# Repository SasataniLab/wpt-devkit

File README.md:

# wpt-devkit-v0.1 SCPI Command Set
Hardware tool and Arduino library for developing wireless power applications.

## Command reference
[SCPI command reference](./docs/SCPI.md)

## Arduino IDE
### Installation
Add `wpt-io-arduino.zip` in release.
- Sketch -> Include Library -> Add .ZIP Library

### Dependencies
**Manual ZIP install**
- [bschulz1701/PAC1720_Library](https://github.com/bschulz1701/PAC1720_Library)

**Arduino Library Manager**
- [WifWaf/MCP45HVX1](https://github.com/WifWaf/MCP45HVX1)

### Update
You need to manually uninstall to update. We plan to add this to Arduino Library Manager to automate this in the future.

## Examples
See [Examples](./firmware/wpt-io-arduino/examples) for example Arduino sketches

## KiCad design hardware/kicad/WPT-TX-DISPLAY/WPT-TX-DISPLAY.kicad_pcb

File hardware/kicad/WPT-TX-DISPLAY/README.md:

# WPT-TX-DISPLAY: 表示基板（仮設計）

送電基板 `WPT-01-TRANSMITTER`（`../WPT-TX`、改訂 7）の J2（2 × 6）に挿す表示用の子基板（v0.2）。0.96 型の IPS TFT（80 × 160 画素、ST7735S）を 1 個載せる。3.3 V だけで動く。設計の考え方、重なり方の図、表示器の入手先、確かめていないことは [`docs/stm32-tx/display_shield_study.md`](../../../docs/stm32-tx/display_shield_study.md) にまとめた。

状態（2026-11-17）: 回路図の ERC 0 件、基板の DRC（回路図との照合つき）0 件。実物では組んでいない。

## ファイル

| ファイル | 内容 |
|---|---|
| `WPT-TX-DISPLAY.kicad_sch` / `.kicad_pcb` / `.kicad_pro` | 回路図（1 枚）、基板（2 層、30.4 × 14.8 mm）、プロジェクト（設計ルールは送電基板と同じ） |
| `lib/` | 表示器のシンボルとフットプリント（`WPT_Display`） |
| `tools/build.sh` | 回路図 → ERC → ネットリスト → 基板 → DRC を通して実行する |
| `tools/gen_sch.py`、`tools/schgen.py` | 回路図を書くスクリプトと、その下請け |
| `tools/make_board.py` | ネットリストから基板を作る（外形、配置、配線、ベタ、シルク） |
| `tools/make_footprint.py` | 表示器のフットプリントを作る。フレキの寸法の出どころもここに書いてある |
| `tools/drawings.py` | 文書の図 3 枚を、送電基板とこの基板のファイルから作る |
| `tools/drc_summary.py` | DRC の結果（JSON）の件数を表示する |
| `fab/export.sh`、`fab/bom_extra.csv` | 製造データの出力と、基板データに無い部品の表（今は空） |

## 作り直す

KiCad 10（`kicad-cli` と `pcbnew` の Python モジュール）が要る。

```sh
cd hardware/kicad/WPT-TX-DISPLAY
sh tools/build.sh        # 終了コード 0 なら ERC・DRC とも 0 件
sh fab/export.sh         # fab/out/ にガーバー、ドリル、BOM、部品座標、図面
python3 tools/drawings.py ../WPT-TX/WPT-01-TRANSMITTER.kicad_pcb WPT-TX-DISPLAY.kicad_pcb \
    ../../../docs/stm32-tx/img/display_plan.png ../../../docs/stm32-tx/img/display_side.png ../../../docs/stm32-tx/img/display_board.png
```

- 回路図と基板はスクリプトが書く。定数や寸法を変えるときはスクリプトを直して `tools/build.sh` を実行する。KiCad で開いて手で直すこともできるが、スクリプトを再実行すると上書きされる。
- 基板の座標は送電基板と同じにしてある。この基板の点 (x, y) は、送電基板の同じ座標の点の 9.9 mm 上にある。
- `fab/out/` は git 管理外。発注用の一式は `../release/WPT-TX-DISPLAY_v0.2/` に置いてある。

## 発注するとき

- 基板: 2 層、1.6 mm、30.4 × 14.8 mm の長方形（角は R1.0）。最小線幅 / 間隔 0.2 / 0.2 mm、ビア 0.6 / 0.3 mm（Tenting vias = レジストで覆う）。
- 実装: 裏面だけ、すべて表面実装（C1、C2、R1、R2、Q1 と、ソケット J1 = Samtec SSM-106-L-DV）。
- **表示器 DS1 は実装業者に買わせず、付けさせない**（DNP: BOM にも部品座標のファイルにも入っておらず、実装図では × 印）。別に買って、基板が届いてから手で付ける。型番は文書の §3、手順は §6.2。
- ほかに要るもの: ポリイミドテープ、両面テープ。ねじとスペーサは要らない（J2 のソケットだけで支える）。
- 挿す向き: 表示器のフレキの折り返しが東（USB コネクタの側）。逆向きにも挿さるが、電源ピンは対称なので壊れない（表示は出ない）。

## ファームウェアから見たピン

| 信号 | MCU のピン | 備考 |
|---|---|---|
| SCK / MOSI | PA5 / PA7（SPI1） | J2 の 5 番 / 3 番。表示器へは書き込みだけ。MISO（PA6、4 番）は使わない |
| CS / DC / RST | PA2 / PA3 / PA4 | J2 の 8 番 / 6 番 / 7 番。いずれも Low で有効（DC は Low がコマンド） |
| バックライト | PB3（TIM2_CH2） | J2 の 10 番。High で点灯。PWM で調光できる。駆動するまでは消灯 |

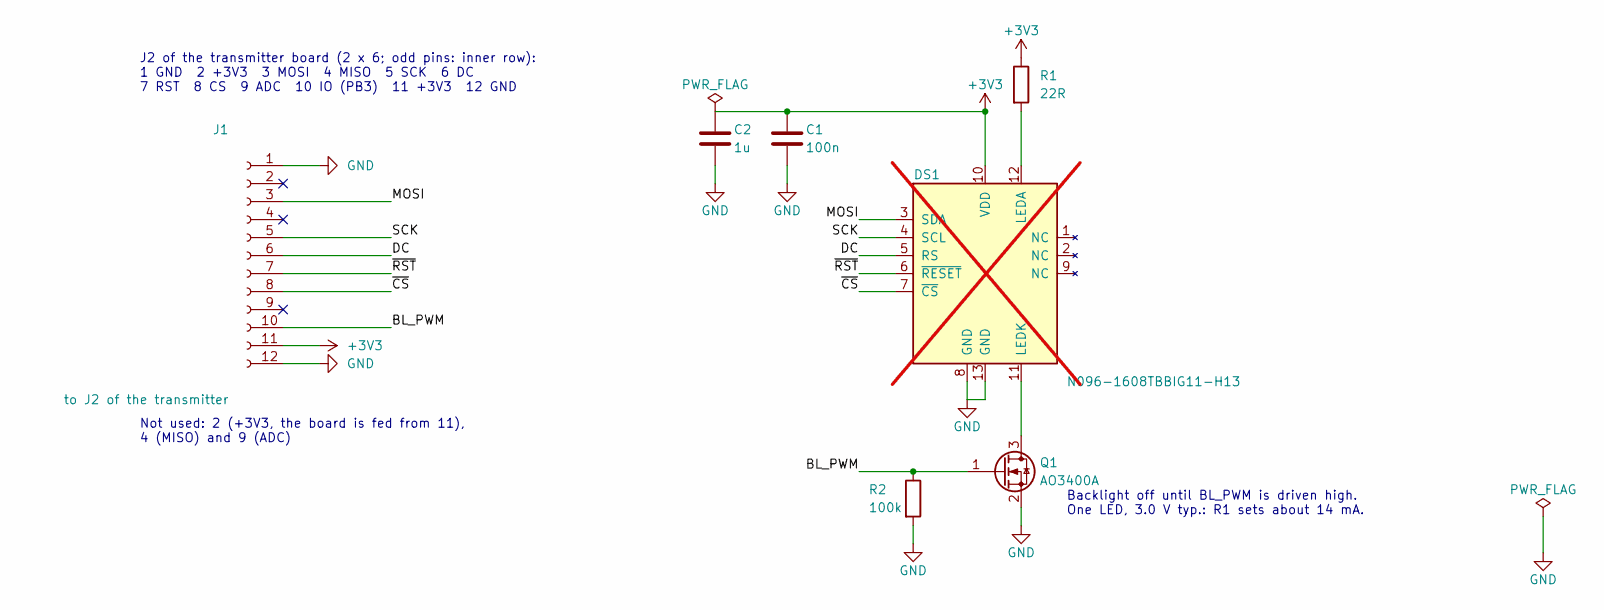
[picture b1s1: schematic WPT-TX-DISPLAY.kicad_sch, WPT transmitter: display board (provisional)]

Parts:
C1: 100n; C_0402_1005Metric; Manufacturer Part Number GCM155R71H104KE02D
C2: 1u; C_0402_1005Metric; Manufacturer Part Number CL05A105KA5NQNC
DS1: N096-1608TBBIG11-H13; TFT_0.96in_80x160_FPC13_P0.7mm_Folded; Manufacturer Part Number N096-1608TBBIG11-H13; not fitted
J1: to J2 of the transmitter; PinSocket_2x06_P2.54mm_Vertical_SMD; Manufacturer Part Number SSM-106-L-DV
Q1: AO3400A; SOT-23; Manufacturer Part Number AO3400A
R1: 22R; R_0402_1005Metric; Manufacturer Part Number RC0402FR-0722RL
R2: 100k; R_0402_1005Metric; Manufacturer Part Number RC0402FR-07100KL

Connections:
+3V3: C1.1, C2.1, DS1.10 (VDD), J1.11, R1.1
/BL_PWM: J1.10, Q1.1 (G), R2.1
/DC: DS1.5 (RS), J1.6
/MOSI: DS1.3 (SDA), J1.3
/SCK: DS1.4 (SCL), J1.5
/~CS: DS1.7 (~CS), J1.8
/~RST: DS1.6 (~RESET), J1.7
GND: C1.2, C2.2, DS1.8 (GND), DS1.13 (GND), J1.1, J1.12, Q1.2 (S), R2.2
unnamed: DS1.12 (LEDA), R1.2
unnamed: DS1.11 (LEDK), Q1.3 (D)

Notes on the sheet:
Not used: 2 (+3V3, the board is fed from 11), 4 (MISO) and 9 (ADC)
J2 of the transmitter board (2 x 6; odd pins: inner row): 1 GND 2 +3V3 3 MOSI 4 MISO 5 SCK 6 DC 7 RST 8 CS 9 ADC 10 IO (PB3) 11 +3V3 12 GND
Backlight off until BL_PWM is driven high. One LED, 3.0 V typ.: R1 sets about 14 mA.

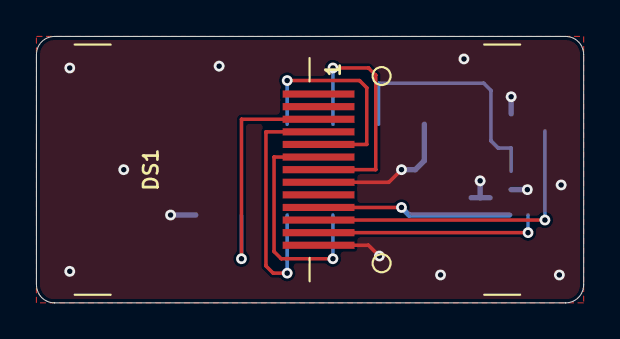
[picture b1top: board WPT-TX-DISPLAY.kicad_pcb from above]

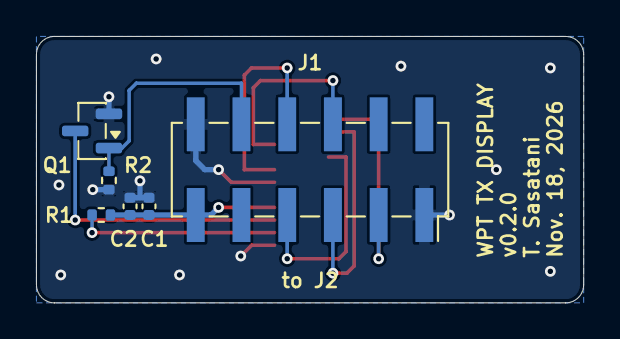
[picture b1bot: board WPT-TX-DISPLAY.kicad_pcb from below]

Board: 2 copper layers, 30.4 x 14.8 mm, 7 parts (6 on the bottom side), 10 nets.

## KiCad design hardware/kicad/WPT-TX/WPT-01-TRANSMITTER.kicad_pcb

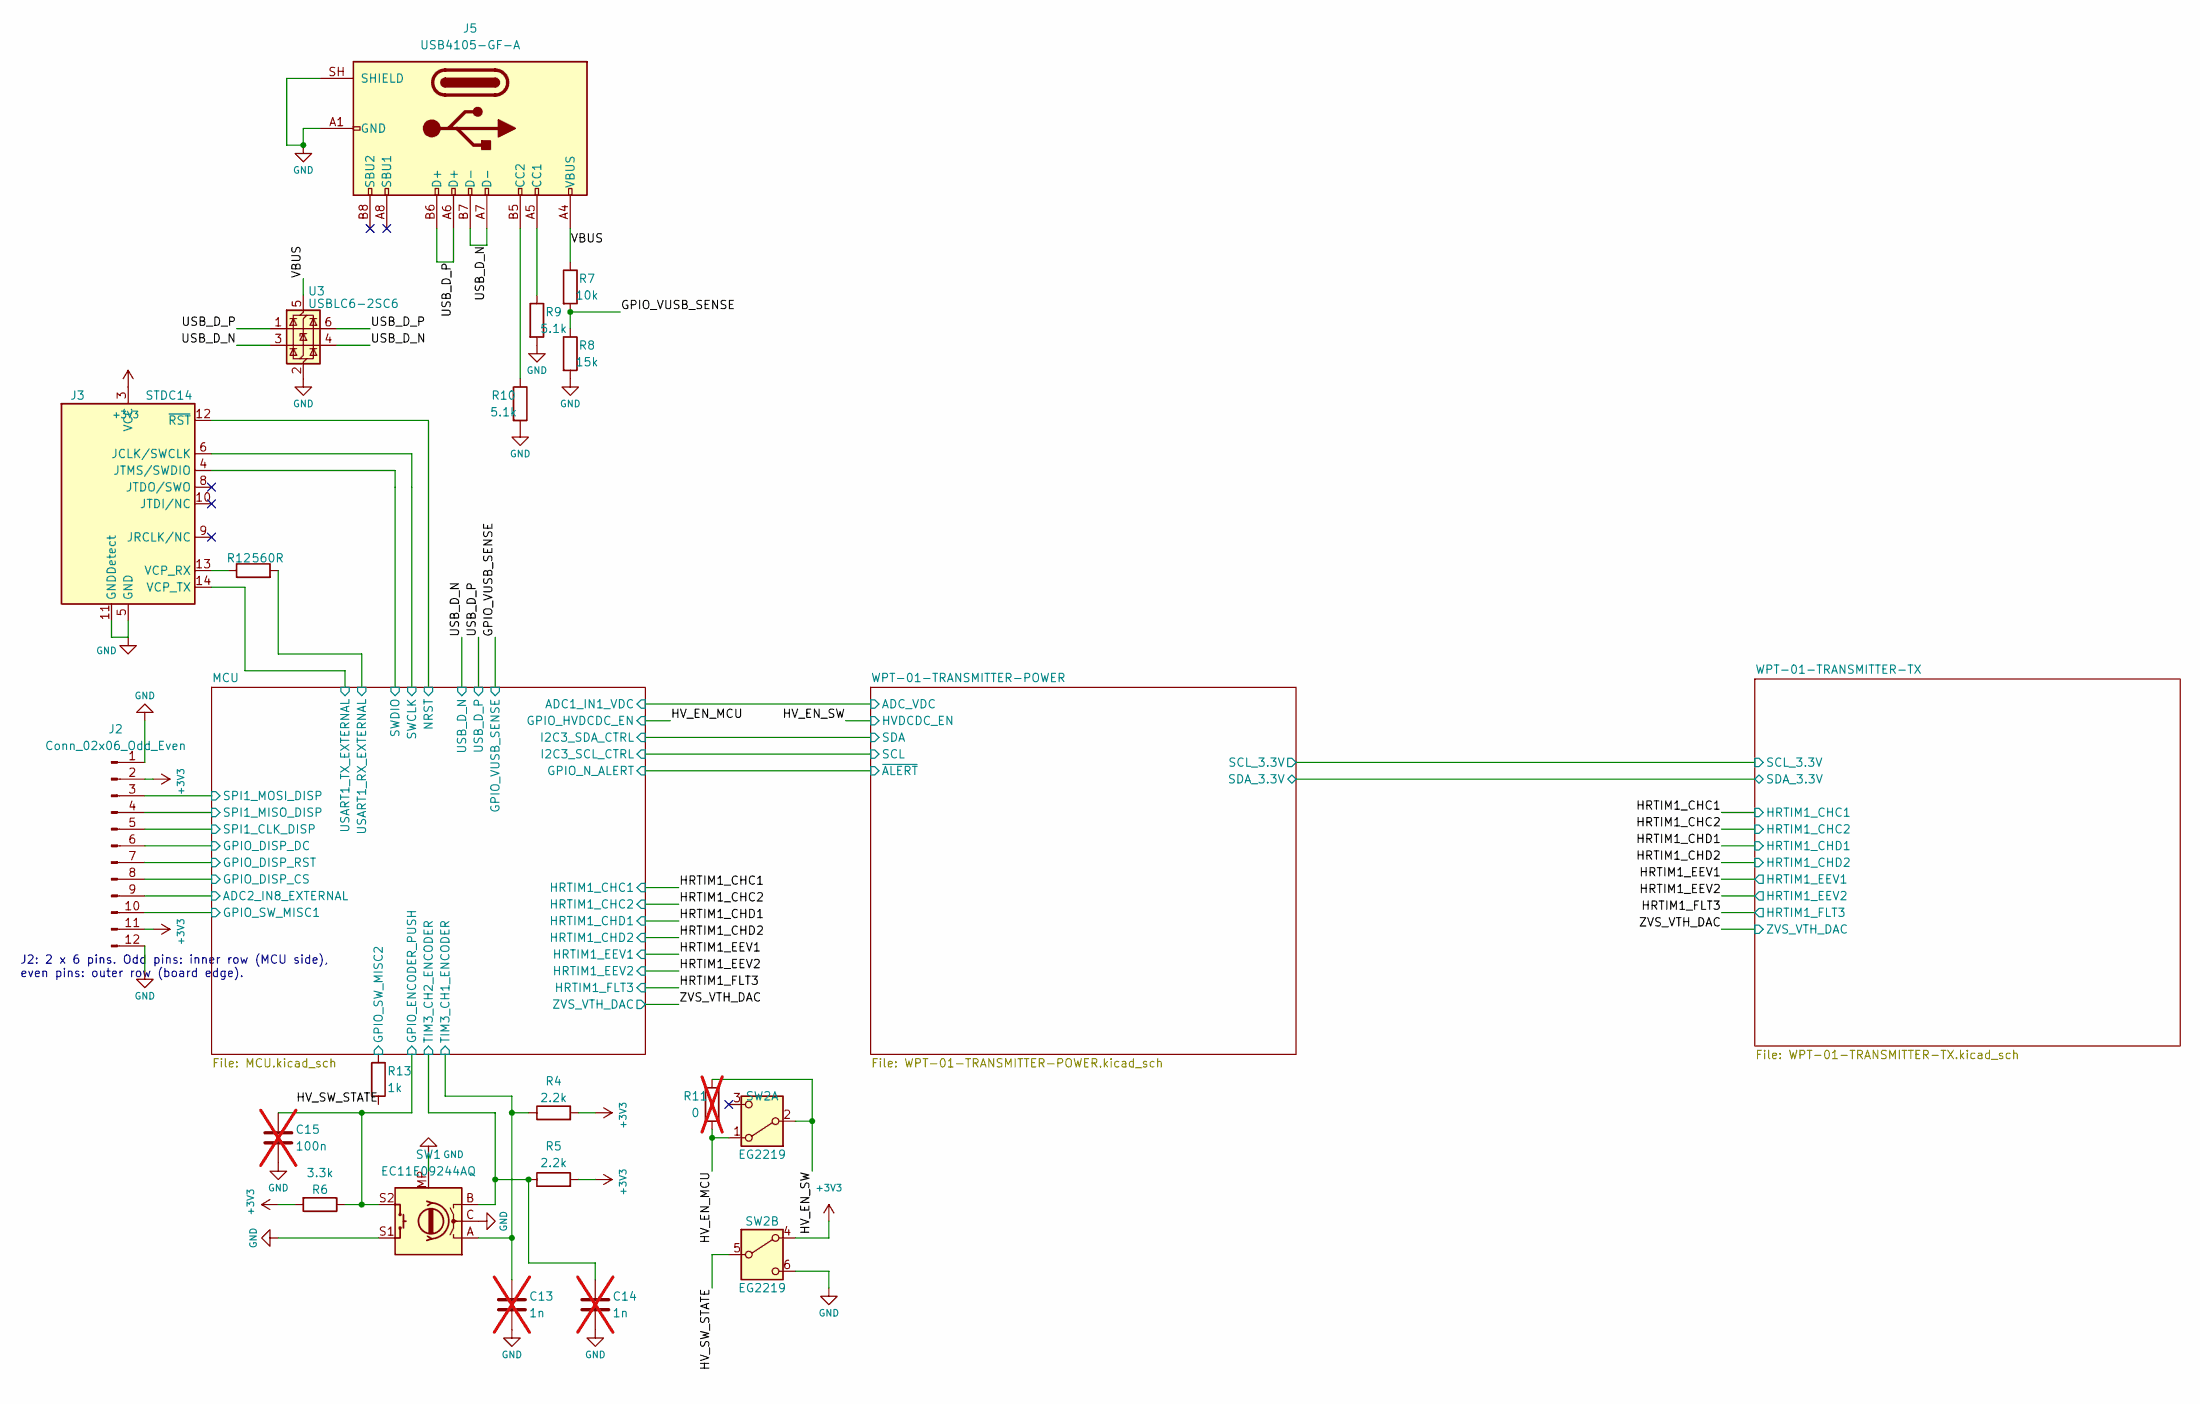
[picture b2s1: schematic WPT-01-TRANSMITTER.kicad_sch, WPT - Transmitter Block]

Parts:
C13, C14: 1n; C_0402_1005Metric; Manufacturer Part Number GRM155R71H102KA01D; not fitted
C15: 100n; C_0402_1005Metric; Manufacturer Part Number GCM155R71H104KE02D; not fitted
J2: Conn_02x06_Odd_Even; PinHeader_2x06_P2.54mm_Vertical; Manufacturer Part Number 61301221121
J3: STDC14; FTSH-107-01-L-D-K_2x07_P1.27mm_Vertical; Manufacturer Part Number FTSH-107-01-L-D-K
J5: USB4105-GF-A; USB_C_Receptacle_GCT_USB4105-xx-A_16P_TopMnt_Horizontal; Manufacturer Part Number USB4105-GF-A
R4, R5: 2.2k; R_0402_1005Metric; Manufacturer Part Number RC0402FR-072K2L
R6: 3.3k; R_0402_1005Metric; Manufacturer Part Number RC0402FR-073K3L
R7: 10k; R_0402_1005Metric; Manufacturer Part Number RC0402FR-0710KL
R8: 15k; R_0402_1005Metric; Manufacturer Part Number RC0402FR-0715KL
R9, R10: 5.1k; R_0402_1005Metric; Manufacturer Part Number RC0402FR-075K1L
R11: 0; R_0402_1005Metric; Manufacturer Part Number RC0402FR-070RL; not fitted
R12: 560R; R_0402_1005Metric; Manufacturer Part Number RC0402FR-07560RL
R13: 1k; R_0402_1005Metric; Manufacturer Part Number RC0402FR-071KL
SW1: EC11E09244AQ; RotaryEncoder_Alps_EC11E-Switch_Vertical_H20mm; Manufacturer Part Number EC11E09244AQ
SW2: EG2219; SW_E-Switch_EG2219_DPDT_Angled; Manufacturer Part Number EG2219
U3: USBLC6-2SC6; SOT-23-6; Manufacturer Part Number USBLC6-2SC6

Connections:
+3V3: J2.2, J2.11, J3.3 (VCC), R4.2, R5.2, R6.2, SW2.4 (A); also elsewhere on the board
/GPIO_VUSB_SENSE: R7.2, R8.1; also elsewhere on the board
/HV_EN_MCU: R11.2, SW2.1 (A); also elsewhere on the board
/HV_EN_SW: R11.1, SW2.2 (B); also elsewhere on the board
/HV_SW_STATE: R13.2, SW2.5 (B)
/MCU/ADC2_IN8_EXTERNAL: J2.9; also elsewhere on the board
/MCU/GPIO_DISP_CS: J2.8; also elsewhere on the board
/MCU/GPIO_DISP_DC: J2.6; also elsewhere on the board
/MCU/GPIO_DISP_RST: J2.7; also elsewhere on the board
/MCU/GPIO_ENCODER_PUSH: C15.1, R6.1, SW1.S2; also elsewhere on the board
/MCU/GPIO_SW_MISC1: J2.10; also elsewhere on the board
/MCU/GPIO_SW_MISC2: R13.1; also elsewhere on the board
/MCU/NRST: J3.12 (~RST); also elsewhere on the board
/MCU/SPI1_CLK_DISP: J2.5; also elsewhere on the board
/MCU/SPI1_MISO_DISP: J2.4; also elsewhere on the board
/MCU/SPI1_MOSI_DISP: J2.3; also elsewhere on the board
/MCU/SWCLK: J3.6 (JCLK/SWCLK); also elsewhere on the board
/MCU/SWDIO: J3.4 (JTMS/SWDIO); also elsewhere on the board
/MCU/TIM3_CH1_ENCODER: C13.1, R4.1, SW1.A; also elsewhere on the board
/MCU/TIM3_CH2_ENCODER: C14.1, R5.1, SW1.B; also elsewhere on the board
/MCU/USART1_RX_EXTERNAL: R12.2; also elsewhere on the board
/MCU/USART1_TX_EXTERNAL: J3.14 (VCP_TX); also elsewhere on the board
/USB_D_N: J5.A7 (D-), J5.B7 (D-), U3.3 (I/O2), U3.4 (I/O2); also elsewhere on the board
/USB_D_P: J5.A6 (D+), J5.B6 (D+), U3.1 (I/O1), U3.6 (I/O1); also elsewhere on the board
/VBUS: J5.A4 (VBUS), J5.A9 (VBUS), J5.B4 (VBUS), J5.B9 (VBUS), R7.1, U3.5 (VBUS)
GND: C13.2, C14.2, C15.2, J2.1, J2.12, J3.5 (GND), J3.7 (GND), J3.11 (GNDDetect), J5.A1 (GND), J5.A12 (GND), J5.B1 (GND), J5.B12 (GND), J5.SH (SHIELD), R8.2, R9.2, R10.2, SW1.C, SW1.MP, SW1.S1, SW2.6 (C), U3.2 (GND); also elsewhere on the board
unnamed: J3.13 (VCP_RX), R12.1
unnamed: J5.A5 (CC1), R9.1
unnamed: J5.B5 (CC2), R10.1

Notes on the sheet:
J2: 2 x 6 pins. Odd pins: inner row (MCU side), even pins: outer row (board edge).

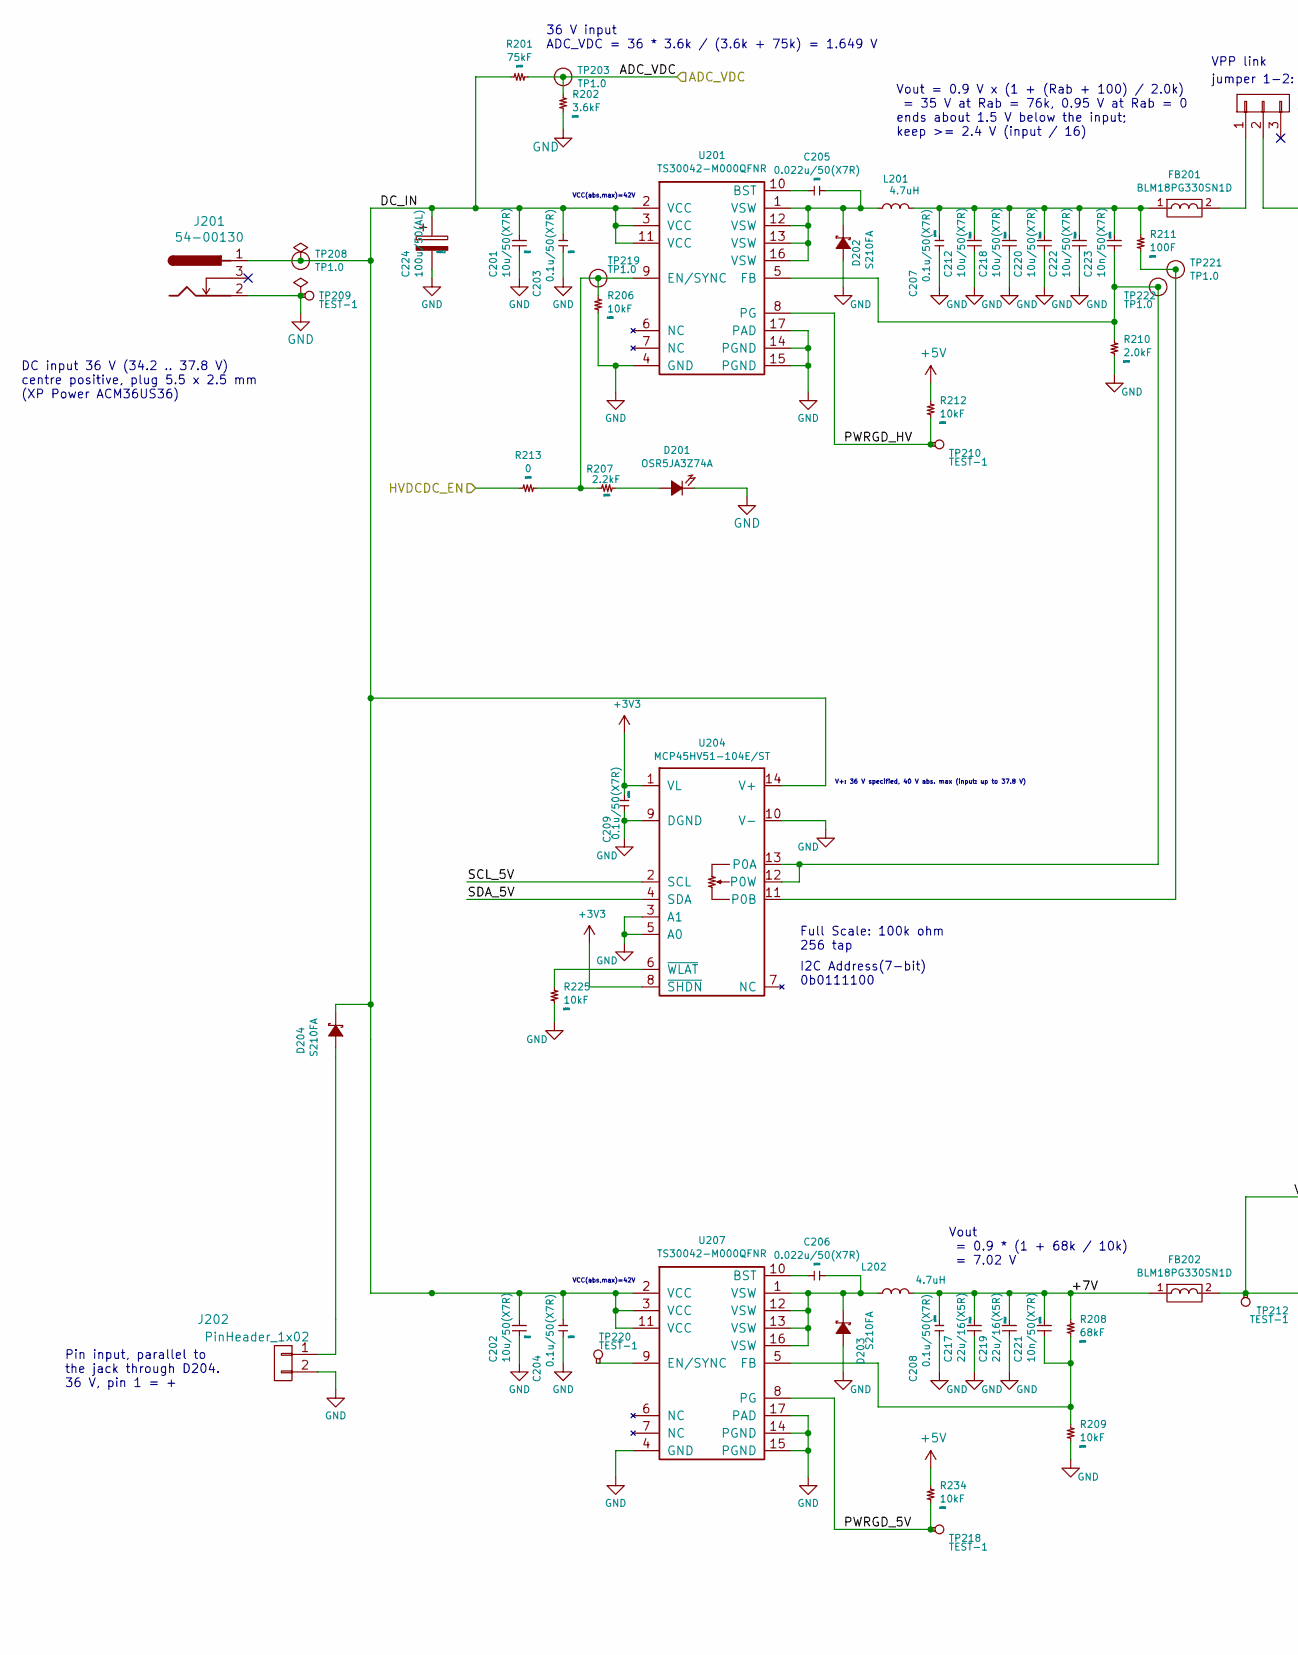
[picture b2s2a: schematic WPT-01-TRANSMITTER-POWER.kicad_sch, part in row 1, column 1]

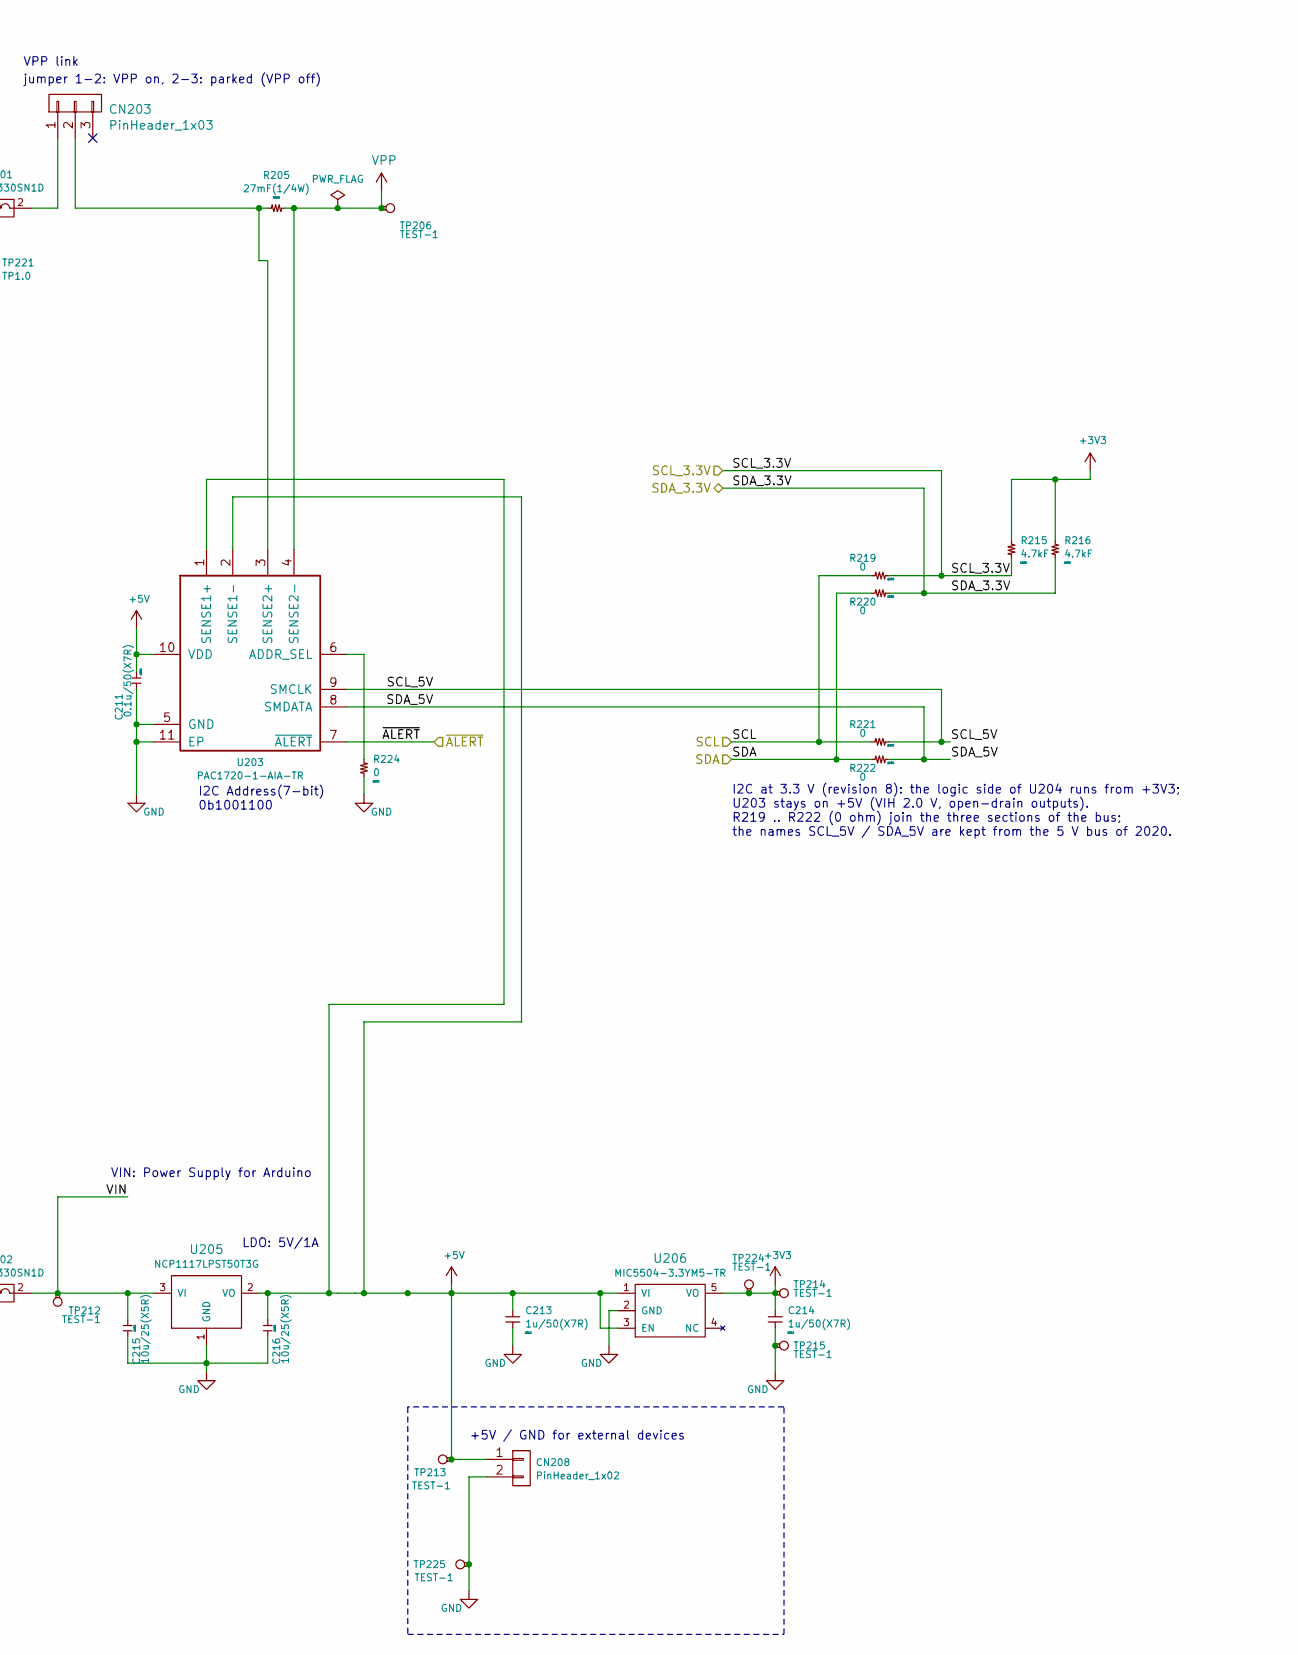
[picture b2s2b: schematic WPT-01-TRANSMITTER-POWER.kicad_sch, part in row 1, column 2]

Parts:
C201, C202, C212, C218, C220, C222: 10u/50(X7R); GRM31; Manufacturer Part Number CL31B106KBHNNNE
C203, C204, C207, C208, C209, C211: 0.1u/50(X7R); GRM15; Manufacturer Part Number GCM155R71H104KE02D
C205, C206: 0.022u/50(X7R); GRM15; Manufacturer Part Number GRM155R71H223KA12D
C213, C214: 1u/50(X7R); GRM21; Manufacturer Part Number CL21B105KBFNNNG
C215, C216: 10u/25(X5R); GRM18; Manufacturer Part Number GRM188R61E106MA73D
C217, C219: 22u/16(X5R); GRM21; Manufacturer Part Number CL21A226MOCLRNC
C221, C223: 10n/50(X7R); GRM15; Manufacturer Part Number CC0402KRX7R9BB103
C224: 100u/50(AL); CP_Elec_8x10; Manufacturer Part Number EEE-FK1H101P
CN203: PinHeader_1x03; ULO-PH409-1x3SX1; Manufacturer Part Number 61300311121
CN208: PinHeader_1x02; ULO-PH409-1x2SX1; Manufacturer Part Number 61300211121
D201: OSR5JA3Z74A; LED_D3.0mm; Manufacturer Part Number OSR5JA3Z74A
D202, D203, D204: S210FA; SOD-123FA_OnSemi; Manufacturer Part Number S210FA
FB201, FB202: BLM18PG330SN1D; BLM18; Manufacturer Part Number BLM18PG330SN1D
J201: 54-00130; 54-00129; Manufacturer Part Number 54-00130
J202: PinHeader_1x02; ULO-PH409-1x2SX1; Manufacturer Part Number 61300211121
L201, L202: 4.7uH; NR5040; Manufacturer Part Number LSXND5050YAL4R7NMG
R201: 75kF; R_0402; Manufacturer Part Number RC0402FR-0775KL
R202: 3.6kF; R_0402; Manufacturer Part Number RC0402FR-073K6L
R205: 27mF(1/4W); R_1206; Manufacturer Part Number RL1206FR-070R027L
R206, R209, R212, R225, R234: 10kF; R_0402; Manufacturer Part Number RC0402FR-0710KL
R207: 2.2kF; R_0402; Manufacturer Part Number RC0402FR-072K2L
R208: 68kF; R_0402; Manufacturer Part Number RC0402FR-0768KL
R210: 2.0kF; R_0402; Manufacturer Part Number RC0402FR-072KL
R211: 100F; R_0402; Manufacturer Part Number RC0402FR-07100RL
R213, R219, R220, R221, R222, R224: 0; R_0402; Manufacturer Part Number RC0402FR-070RL
R215, R216: 4.7kF; R_0402; Manufacturer Part Number RC0402FR-074K7L
TP203, TP208, TP219, TP221, TP222: TP1.0; TP_1mm
TP206, TP209, TP210, TP212, TP213, TP214, TP215, TP218, TP220, TP224, TP225: TEST-1; PTH_1mm
U201, U207: TS30042-M000QFNR; QFN-16-1EP_3x3mm_Pitch0.5mm_Semtech; Manufacturer Part Number TS30042-M000QFNR
U203: PAC1720-1-AIA-TR; DFN-10-1EP_3x3mm_Pitch0.5mm_microchip_9Q; Manufacturer Part Number PAC1720-1-AIA-TR
U204: MCP45HV51-104E/ST; TSSOP-14_4.4x5mm_P0.65mm; Manufacturer Part Number MCP45HV51-104E/ST
U205: NCP1117LPST50T3G; SOT-223-3_TabPin2; Manufacturer Part Number NCP1117LPST50T3G
U206: MIC5504-3.3YM5-TR; microchip_SOT23-5LD-PL-1; Manufacturer Part Number MIC5504-3.3YM5-TR

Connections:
+3V3: C209.2, C214.1, R215.2, R216.2, TP214.1 (~_1), TP224.1 (~_1), U204.1 (VL), U204.8 (~SHDN), U206.5 (VO); also elsewhere on the board
+5V: C211.2, C213.1, C216.1, CN208.1, R212.2, R234.2, TP213.1 (~_1), U203.1 (SENSE1+), U203.2 (SENSE1-), U203.10 (VDD), U205.2 (VO), U206.1 (VI), U206.3 (EN); also elsewhere on the board
/HV_EN_SW: R213.2; also elsewhere on the board
/WPT-01-TRANSMITTER-POWER/+7V: C208.1, C217.1, C219.1, C221.1, FB202.1, L202.2, R208.2
/WPT-01-TRANSMITTER-POWER/ADC_VDC: R201.1, R202.2, TP203.1 (~_1); also elsewhere on the board
/WPT-01-TRANSMITTER-POWER/DC_IN: C201.1, C202.1, C203.1, C204.1, C224.1, D204.1 (K), J201.1, R201.2, TP208.1 (~_1), U201.2 (VCC), U201.3 (VCC), U201.11 (VCC), U204.14 (V+), U207.2 (VCC), U207.3 (VCC), U207.11 (VCC)
/WPT-01-TRANSMITTER-POWER/PWRGD_5V: R234.1, TP218.1 (~_1), U207.8 (PG)
/WPT-01-TRANSMITTER-POWER/PWRGD_HV: R212.1, TP210.1 (~_1), U201.8 (PG)
/WPT-01-TRANSMITTER-POWER/SCL: R219.2, R221.2; also elsewhere on the board
/WPT-01-TRANSMITTER-POWER/SCL_3.3V: R215.1, R219.1; also elsewhere on the board
/WPT-01-TRANSMITTER-POWER/SCL_5V: R221.1, U203.9 (SMCLK), U204.2 (SCL)
/WPT-01-TRANSMITTER-POWER/SDA: R220.2, R222.2; also elsewhere on the board
/WPT-01-TRANSMITTER-POWER/SDA_3.3V: R216.1, R220.1; also elsewhere on the board
/WPT-01-TRANSMITTER-POWER/SDA_5V: R222.1, U203.8 (SMDATA), U204.4 (SDA)
/WPT-01-TRANSMITTER-POWER/VIN: C215.1, FB202.2, TP212.1 (~_1), U205.3 (VI)
/WPT-01-TRANSMITTER-POWER/~ALERT: U203.7 (~ALERT); also elsewhere on the board
GND: C201.2, C202.2, C203.2, C204.2, C207.2, C208.2, C209.1, C211.1, C212.2, C213.2, C214.2, C215.2, C216.2, C217.2, C218.2, C219.2, C220.2, C222.2, C224.2, CN208.2, D201.1 (K), D202.2 (A), D203.2 (A), J201.2, J202.2, R202.1, R206.1, R209.1, R210.1, R224.1, R225.1, TP209.1 (~_1), TP215.1 (~_1), TP225.1 (~_1), U201.4 (GND), U201.14 (PGND), U201.15 (PGND), U201.17 (PAD), U203.5 (GND), U203.11 (EP), U204.3 (A1), U204.5 (A0), U204.9 (DGND), U204.10 (V-), U205.1 (GND), U206.2 (GND), U207.4 (GND), U207.14 (PGND), U207.15 (PGND), U207.17 (PAD); also elsewhere on the board
unnamed: C207.1, C212.1, C218.1, C220.1, C222.1, C223.1, FB201.1, L201.2, R211.2
unnamed: CN203.1, FB201.2
unnamed: CN203.2, R205.2, U203.3 (SENSE2+)
unnamed: D201.2 (A), R207.2
unnamed: C205.2, D202.1 (K), L201.1, U201.1 (VSW), U201.12 (VSW), U201.13 (VSW), U201.16 (VSW)
unnamed: C206.2, D203.1 (K), L202.1, U207.1 (VSW), U207.12 (VSW), U207.13 (VSW), U207.16 (VSW)
unnamed: D204.2 (A), J202.1
unnamed: R206.2, R207.1, R213.1, TP219.1 (~_1), U201.9 (EN/SYNC)
unnamed: TP220.1 (~_1), U207.9 (EN/SYNC)
unnamed: R211.1, TP221.1 (~_1), U204.11 (P0B)
unnamed: C223.2, R210.2, TP222.1 (~_1), U201.5 (FB), U204.12 (P0W), U204.13 (P0A)
unnamed: C205.1, U201.10 (BST)
unnamed: R224.2, U203.6 (ADDR_SEL)
unnamed: R225.2, U204.6 (~WLAT)
unnamed: C206.1, U207.10 (BST)
unnamed: C221.2, R208.1, R209.2, U207.5 (FB)
VPP: R205.1, TP206.1 (~_1), U203.4 (SENSE2-); also elsewhere on the board

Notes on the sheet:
Pin input, parallel to the jack through D204. 36 V, pin 1 = +
Vout = 0.9 V x (1 + (Rab + 100) / 2.0k) = 35 V at Rab = 76k, 0.95 V at Rab = 0 ends about 1.5 V below the input; keep >= 2.4 V (input / 16)
36 V input ADC_VDC = 36 * 3.6k / (3.6k + 75k) = 1.649 V
Full Scale: 100k ohm 256 tap
VCC(abs,max)=42V
DC input 36 V (34.2 .. 37.8 V) centre positive, plug 5.5 x 2.5 mm (XP Power ACM36US36)
Vout = 0.9 * (1 + 68k / 10k) = 7.02 V
LDO: 5V/1A
VPP link
VIN: Power Supply for Arduino
I2C Address(7-bit) 0b1001100
V+: 36 V specified, 40 V abs. max (input: up to 37.8 V)
jumper 1-2: VPP on, 2-3: parked (VPP off)
+5V / GND for external devices
I2C Address(7-bit) 0b0111100
I2C at 3.3 V (revision 8): the logic side of U204 runs from +3V3; U203 stays on +5V (VIH 2.0 V, open-drain outputs). R219 .. R222 (0 ohm) join the three sections of the bus; the names SCL_5V / SDA_5V are kept from the 5 V bus of 2020.
